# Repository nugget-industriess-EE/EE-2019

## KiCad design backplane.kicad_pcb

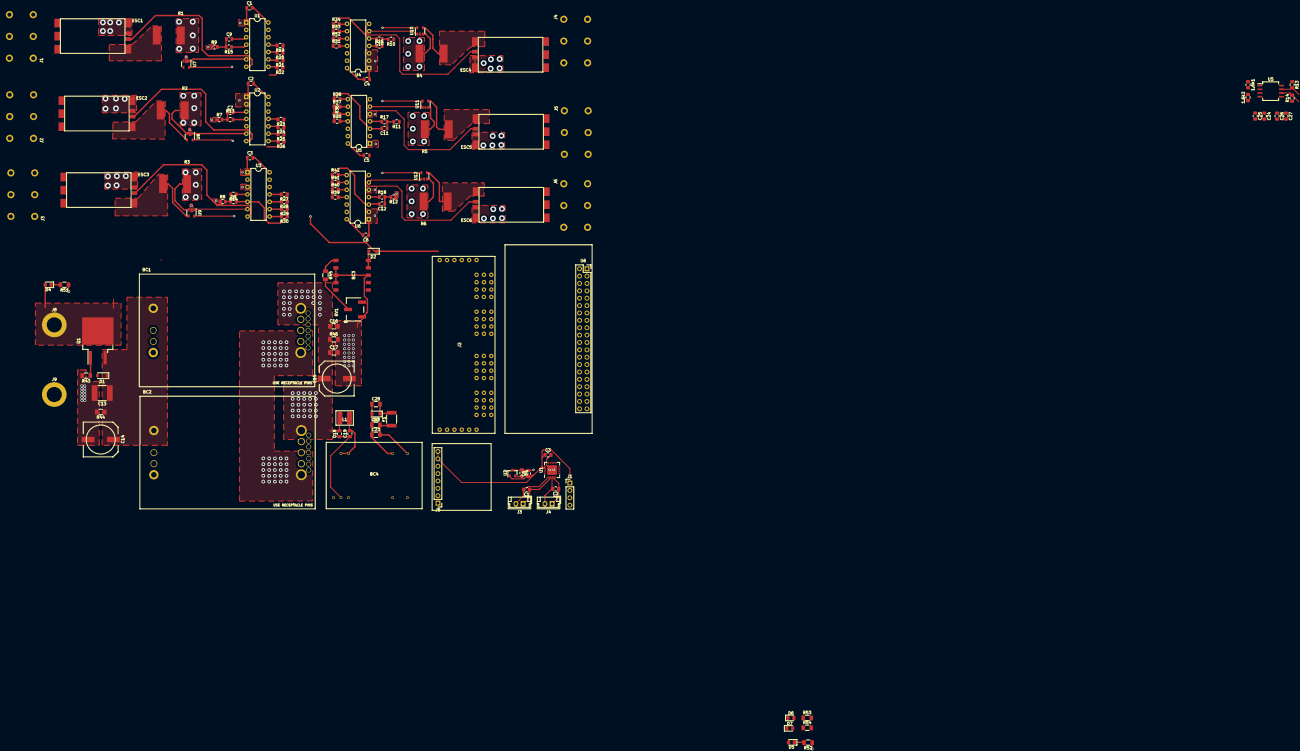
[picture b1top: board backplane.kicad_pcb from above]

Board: 4 copper layers, 135 parts (0 on the bottom side), 102 nets.

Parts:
1.6k1, 1.6k2: R_Small; R_0805_2012Metric_Pad1.15x1.40mm_HandSolder
BC1, BC2: DS_Q48SC12050NRII; DS_Q48SC12050
BC3: R-78AA-1.0; R78AA-1.0
BC4: JTF1524S05
C1, C2, C3, C4, C5, C6: .1uF; C_0805_2012Metric
C1#2, C2#2: 100pF; C_0805_2012Metric_Pad1.15x1.40mm_HandSolder
C3#2, C4#2, C5#2: 0.1uF; C_0805_2012Metric_Pad1.15x1.40mm_HandSolder
C7, C8, C9, C10, C11, C12: 10nF; C_0805_2012Metric
C13: 10uF; C_2220_SMD
C14: 100uF; PCR1J101MCL1GS
C15: 330uF; PCR1J101MCL1GS
C16, C22: 10uF; C_1206_SMD
C17, C23: 1uF; C_1206_SMD
C18, C19: 2.2uF; C_0805_SMD
C24, C26: 0.01u; C_0805_2012Metric_Pad1.15x1.40mm_HandSolder
C25, C27: 0.1u; C_0805_2012Metric_Pad1.15x1.40mm_HandSolder
C28: 47uF; C_1206_SMD
D1: 12V; D_SOD-123
D2: D_Small_ALT; D_SOD-123F
D3: SMBJ5.0A-13-F; D_SOD-123F
D4, D5, D6, D7: LED; LED_0805_2012Metric_Pad1.15x1.40mm_HandSolder
ESC1, ESC2, ESC3, ESC4, ESC5, ESC6: ESC
F1: MF-MSMF250/16X-2; R_1812_SMD
J1, J2, J3, J4, J5, J6: Conn_01x03_Female; Wago Terminal Blocks
J1#2: Bar02; PinHeader_1x04_P2.54mm_Vertical
J2#2: Conn_02x15_Top_Bottom; PCA9685
J3#2, J4#2: Conn_01x02; JST_EH_B02B-EH-A_1x02_P2.50mm_Vertical
J5#2: LSM303
J8, J9: Conn_01x01; 7466004
L1: 12uH; SDE0403A-120M
Q1: Q_PMOS_GDS; TO-263-2
R1, R2, R3, R4, R5, R6: WSLP59311L000FEB; Shunt Resistor
R7, R8, R9, R10, R11, R12: 10k; R_0805_2012Metric
R13, R14: 1.6k; R_0805_2012Metric_Pad1.15x1.40mm_HandSolder
R13#2, R14#2, R15, R16, R17, R18: 100; R_0805_2012Metric
R19, R20, R21, R22, R24, R25, R26, R28, R29, R30, R36, R37, R38, R40, R41, R42: 1k; R_0805_2012Metric_Pad1.15x1.40mm_HandSolder
R23, R27, R31, R32, R33, R34, R35, R39: R_Small; R_0805_2012Metric_Pad1.15x1.40mm_HandSolder
R43: 100k; R_1206_SMD
R44: 12K; R_1206_SMD
R45: 470K; R_1206_SMD
R46: 3.3K; C_1206_SMD
R51: 2.4K; C_1206_SMD
R52, R53, R54: 600; C_1206_SMD
RV1: 200k; 3269W-1-204GLF
U1, U2, U3, U4, U5#2, U6#2: PIC16F15323; DIP-14_W7.62mm
U1#2: MAX6581; QFN-20-1EP_5x5mm_P0.65mm_EP3.35x3.35mm
U2#2: LM3480-3.3; SOT-23
U5: ADuM1250; SO-8_5.3x6.2mm_P1.27mm
U6: PI_ZERO
U7, U8, U9, U10, U11, U12: TSC888; SOT-23-5

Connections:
5VPI: C26.1, C27.1, C28.2, D3.1, F1.2, R13.1, R14.1, U5.8, U6.2, U6.4
+3V3: C3#2.1, C5#2.1, J1#2.1, J5#2.7, J5#2.8, U1#2.17, U2#2.1, U6.1, U6.17
+5V: BC4.14, C22.2, C23.2, D6.2, F1.1
+5VP: 1.6k1.1, 1.6k2.1, C1.1, C2.1, C3.1, C4.1, C4#2.2, C5.1, C6.1, C24.1, C25.1, D2.1, D7.2, J2#2.5, J2#2.6, J2#2.8, J2#2.11, J2#2.14, J2#2.17, J2#2.20, J2#2.23, J2#2.26, J2#2.29, R7.1, R8.1, R9.1, R10.1, R11.1, R12.1, U1.1, U2.1, U2.2, U2#2.2, U3.1, U3.3, U4.1, U4.2, U4.3, U5.1, U5#2.1, U5#2.5, U6#2.1, U6#2.2, U6#2.5, U7.5, U8.5, U9.5, U10.5, U11.5, U12.5
+12P: BC1.9, BC2.9, BC3.1, BC3.2, BC3.10, C15.1, C16.1, C17.1, C18.2, D5.2, L1.1, R1.1, R2.1, R3.1, R4.1, R5.1, R6.1, R46.1, U7.3, U8.3, U9.3, U10.3, U11.3, U12.3
+48V: D4.2, J8.1, Q1.2
/CS1: U1.6, U7.1
/CS2: U2.6, U8.1
/CS3: U3.6, U9.1
/CS4: U4.6, U10.1
/CS5: U5#2.6, U11.1
/CS6: U6#2.6, U12.1
/PWM1: ESC1.2, J2#2.10, U1.7
/PWM2: ESC2.2, J2#2.13, U2.7
/PWM3: ESC3.2, J2#2.16, U3.7
/PWM4: ESC4.2, J2#2.19, U4.7
/PWM5: ESC5.2, J2#2.22, J2#2.25, J2#2.28, U5#2.7
/PWM6: ESC6.2, U6#2.7
/SCL_iso: 1.6k2.2, J1#2.2, J2#2.3, J5#2.1, U1#2.19, U5.3
/SDA_iso: 1.6k1.2, J1#2.3, J2#2.4, J5#2.2, U1#2.20, U5.2
/VIN+: BC1.1, BC2.1, C13.1, C14.1, D1.1, Q1.3, R44.1
/temp1n: C1#2.2, J3#2.2, U1#2.1
/temp1p: C1#2.1, J3#2.1, U1#2.2
/temp2n: C2#2.2, J4#2.2, U1#2.3
/temp2p: C2#2.1, J4#2.1, U1#2.4
Earth: BC1.2, BC1.4, BC2.2, BC2.4, C13.2, C14.2, J9.1, R43.2, R44.2, R51.1
GND: C4#2.1, C5#2.2, J2#2.1, J2#2.9, J2#2.12, J2#2.15, J2#2.18, J2#2.21, J2#2.24, J2#2.27, J2#2.30, U2#2.3
GNDPWR: BC1.5, BC2.5, BC3.3, BC3.7, BC3.8, BC3.9, BC4.2, BC4.3, C1.2, C2.2, C3.2, C4.2, C5.2, C6.2, C7.2, C8.2, C9.2, C10.2, C11.2, C12.2, C15.2, C16.2, C17.2, C18.1, C19.1, C24.2, C25.2, ESC1.3, ESC1.4, ESC2.3, ESC2.4, ESC3.3, ESC3.4, ESC4.3, ESC4.4, ESC5.3, ESC5.4, ESC6.3, ESC6.4, R19.1, R20.1, R21.1, R22.1, R23.1, R24.1, R25.1, R26.1, R27.1, R28.1, R29.1, R30.1, R31.1, R32.1, R33.1, R34.1, R35.1, R36.1, R37.1, R38.1, R39.1, R40.1, R41.1, R42.1, R46.2, R52.1, R54.1, RV1.1, U1.2, U1.3, U1.5, U1.14, U2.3, U2.5, U2.14, U3.2, U3.5, U3.14, U4.5, U4.14, U5.4, U5#2.2, U5#2.3, U5#2.14, U6#2.3, U6#2.14, U7.2, U8.2, U9.2, U10.2, U11.2, U12.2
GNDS: BC4.16, C3#2.2, C22.1, C23.1, C26.2, C27.2, C28.1, D3.2, J1#2.4, J5#2.6, R53.1, U1#2.21, U5.5, U6.6, U6.9, U6.14, U6.20, U6.25, U6.30, U6.34, U6.39
unnamed: BC3.4, BC3.5, D2.2
unnamed: BC3.6, R45.1
unnamed: BC4.22, BC4.23, C19.2, L1.2
unnamed: C7.1, R7.2, R13#2.2
unnamed: C8.1, R8.2, R14#2.2
unnamed: C9.1, R9.2, R15.2
unnamed: C10.1, R10.2, R16.2
unnamed: C11.1, R11.2, R17.2
unnamed: C12.1, R12.2, R18.2
unnamed: D1.2, Q1.1, R43.1
unnamed: D4.1, R51.2
unnamed: D5.1, R52.2
unnamed: D6.1, R53.2
unnamed: D7.1, R54.2
unnamed: ESC1.1, R1.2, U7.4
unnamed: ESC1.5, J1.1
unnamed: ESC1.6, J1.2
unnamed: ESC1.7, J1.3
unnamed: ESC2.1, R2.2, U8.4
unnamed: ESC2.5, J2.1
unnamed: ESC2.6, J2.2
unnamed: ESC2.7, J2.3
unnamed: ESC3.1, R3.2, U9.4
unnamed: ESC3.5, J3.1
unnamed: ESC3.6, J3.2
unnamed: ESC3.7, J3.3
unnamed: ESC4.1, R4.2, U10.4
unnamed: ESC4.5, J4.1
unnamed: ESC4.6, J4.2
unnamed: ESC4.7, J4.3
unnamed: ESC5.1, R5.2, U11.4
unnamed: ESC5.5, J5.1
unnamed: ESC5.6, J5.2
unnamed: ESC5.7, J5.3
unnamed: ESC6.1, R6.2, U12.4
unnamed: ESC6.5, J6.1
unnamed: ESC6.6, J6.2
unnamed: ESC6.7, J6.3
unnamed: R13#2.1, U2.4
unnamed: R13.2, U5.7, U6.3
unnamed: R14#2.1, U3.4
unnamed: R14.2, U5.6, U6.5
unnamed: R15.1, U1.4
unnamed: R16.1, U4.4
unnamed: R17.1, U5#2.4
unnamed: R18.1, U6#2.4
unnamed: R19.2, U1.11
unnamed: R20.2, U1.10
unnamed: R21.2, U1.9
unnamed: R22.2, U1.8
unnamed: R23.2, U2.11
unnamed: R24.2, U2.10
unnamed: R25.2, U2.9
unnamed: R26.2, U2.8
unnamed: R27.2, U3.11
unnamed: R28.2, U3.10
unnamed: R29.2, U3.9
unnamed: R30.2, U3.8
unnamed: R31.2, U4.11
unnamed: R32.2, U4.10
unnamed: R33.2, U4.9
unnamed: R34.2, U4.8
unnamed: R35.2, U5#2.11
unnamed: R36.2, U5#2.10
unnamed: R37.2, U5#2.9
unnamed: R38.2, U5#2.8
unnamed: R39.2, U6#2.11
unnamed: R40.2, U6#2.10
unnamed: R41.2, U6#2.9
unnamed: R42.2, U6#2.8
unnamed: R45.2, RV1.2, RV1.3
unnamed: U6.12, U6#2.12
unnamed: U6.13, U6#2.13

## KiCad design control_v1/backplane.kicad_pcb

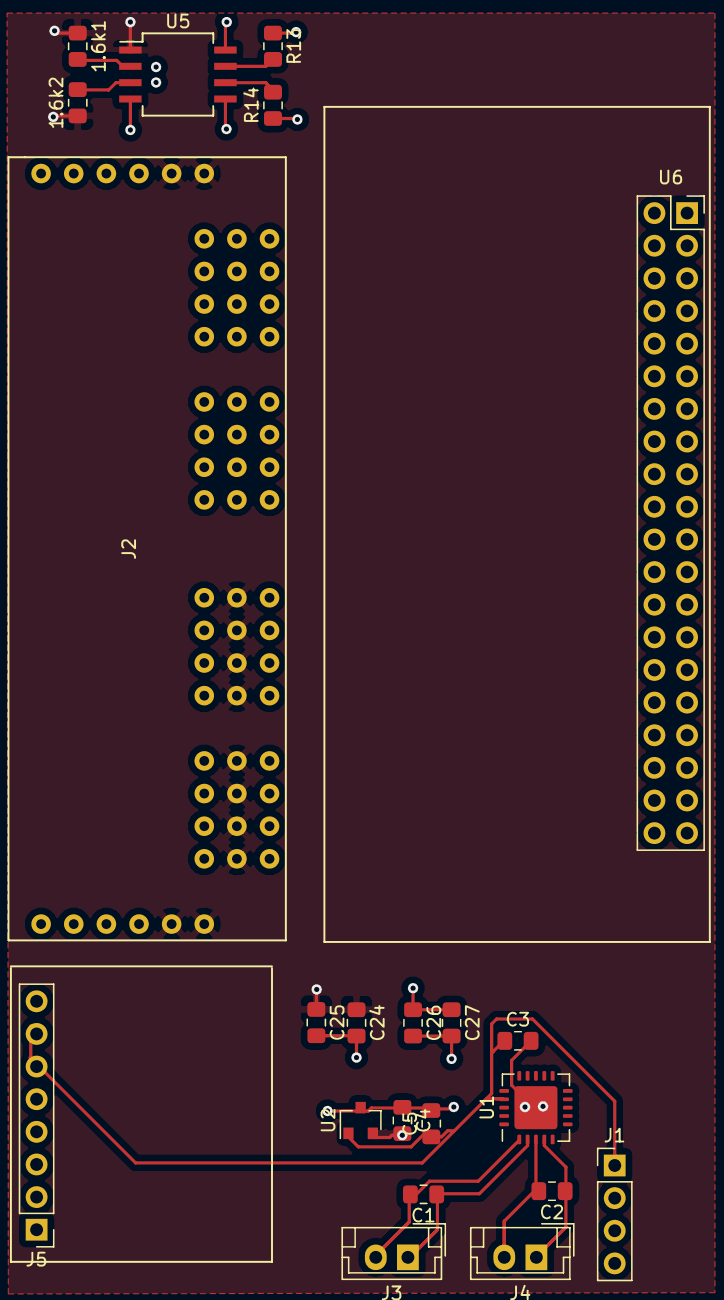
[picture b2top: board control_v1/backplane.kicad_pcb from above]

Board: 4 copper layers, 22 parts (0 on the bottom side), 14 nets.

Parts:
1.6k1, 1.6k2: R_Small; R_0805_2012Metric_Pad1.15x1.40mm_HandSolder
C1, C2: 100nF; C_0805_2012Metric_Pad1.15x1.40mm_HandSolder
C3: 10nF; C_0805_2012Metric_Pad1.15x1.40mm_HandSolder
C4, C5: 0.1uF; C_0805_2012Metric_Pad1.15x1.40mm_HandSolder
C24, C26: 0.01u; C_0805_2012Metric_Pad1.15x1.40mm_HandSolder
C25, C27: 0.1u; C_0805_2012Metric_Pad1.15x1.40mm_HandSolder
J1: Bar02; PinHeader_1x04_P2.54mm_Vertical
J2: Conn_02x15_Top_Bottom; PCA9685
J3, J4: Conn_01x02; JST_EH_B02B-EH-A_1x02_P2.50mm_Vertical
J5: LSM303
R13, R14: 1.6k; R_0805_2012Metric_Pad1.15x1.40mm_HandSolder
U1: SCA3300; QFN-20-1EP_5x5mm_P0.65mm_EP3.35x3.35mm
U2: LM3480-3.3; SOT-23
U5: ADuM1250; SO-8_5.3x6.2mm_P1.27mm
U6: PI_ZERO

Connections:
5VPI: C26.1, C27.1, R13.1, R14.1, U5.8, U6.2, U6.4
+3V3: C1.2, C2.2, C3.2, C5.1, J1.1, J5.7, J5.8, U1.5, U2.1, U6.1, U6.17
+5VP: 1.6k1.1, 1.6k2.1, C4.2, C24.1, C25.1, J2.5, J2.6, J2.8, J2.11, J2.14, J2.17, J2.20, J2.23, J2.26, J2.29, U2.2, U5.1
/PWM5: J2.22, J2.25, J2.28
/Pi/SCL_iso: 1.6k2.2, U5.3
/Pi/SDA_iso: 1.6k1.2, U5.2
/SCL_iso: J1.2, J2.3, J5.1
/SDA_iso: J1.3, J2.4, J5.2
GNDPWR: C4.1, C5.2, C24.2, C25.2, J2.9, J2.12, J2.15, J2.18, J2.21, J2.24, J2.27, J2.30, U2.3, U5.4
GNDS: C26.2, C27.2, J1.4, J5.6, U1.1, U1.11, U1.12, U5.5, U6.6, U6.9, U6.14, U6.20, U6.25, U6.30, U6.34, U6.39
unnamed: C1.1, U1.2
unnamed: C2.1, C3.1, U1.4
unnamed: R13.2, U5.7, U6.3
unnamed: R14.2, U5.6, U6.5
